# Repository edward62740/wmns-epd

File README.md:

# WMNS-EPD
Simple Wi-Fi/BLE enabled e-paper display. Designed for displaying real-time sensor data. Extention of [WMNS](https://github.com/edward62740/Wireless-Mesh-Network-System).</br></br>

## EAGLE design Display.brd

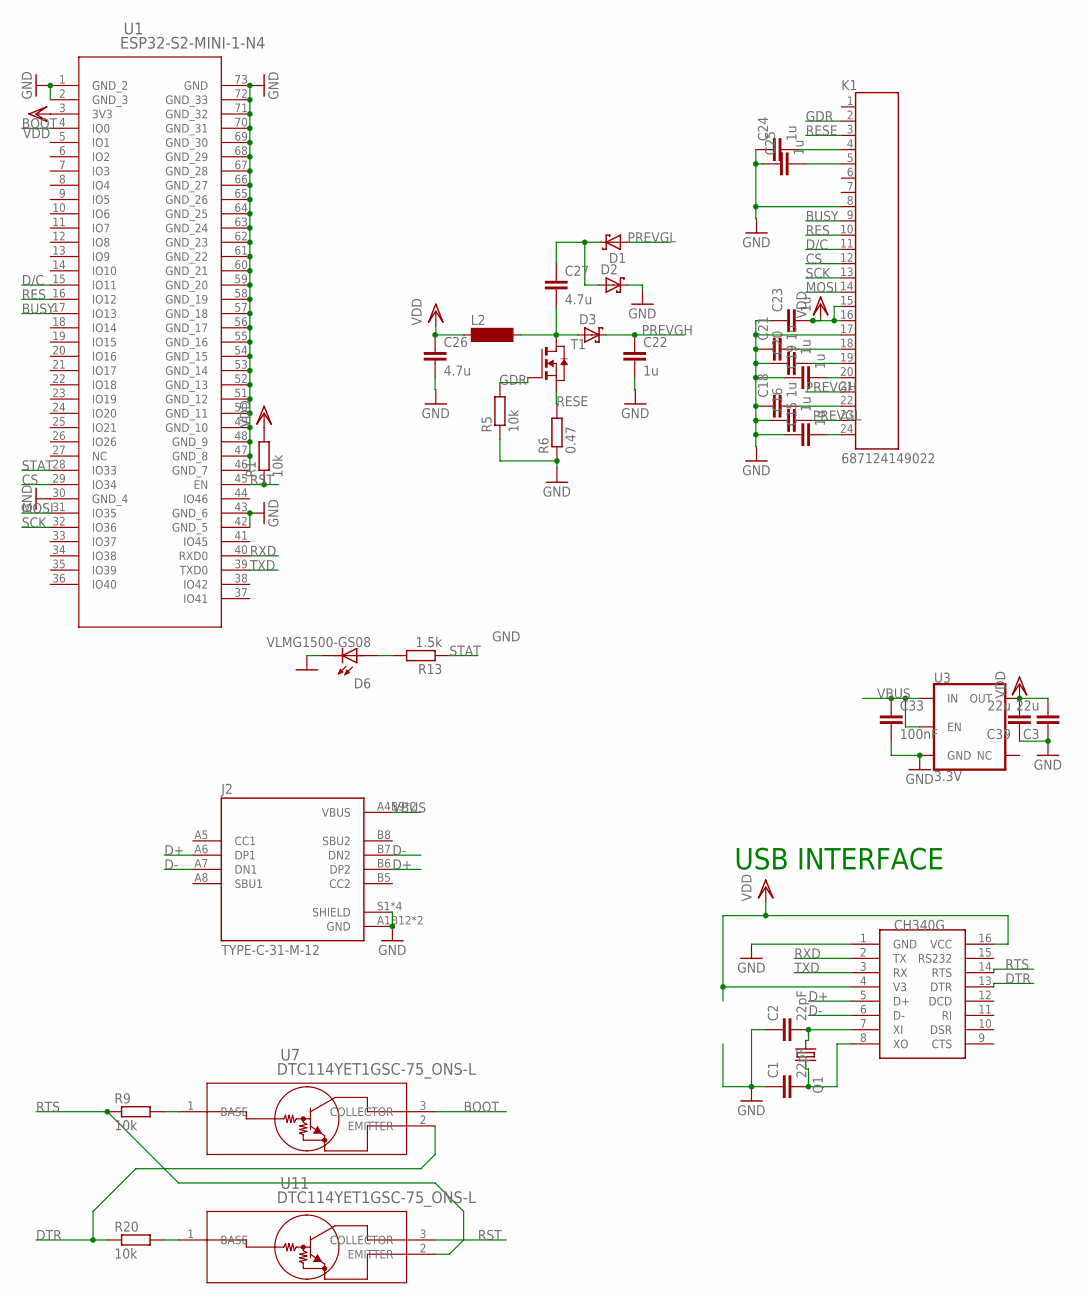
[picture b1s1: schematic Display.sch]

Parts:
C1, C2: 22pF; C0402
C3, C39: 22u; C0603R
C15, C16, C18, C19, C20, C21, C22, C23, C24, C25: 1u; C0402
C26, C27: 4.7u; C0402
C33: 100nF; C0402
D1, D2, D3: 1PS79SB30,115; SOD523
D6: VLMG1500-GS08; LEDC1005X35N
J2: TYPE-C-31-M-12; HRO_TYPE-C-31-M-12
K1: 687124149022
L2: SM-NE29
Q1: KX-7; 3.2X2.5_KX-7
R1, R5, R9, R20: 10k; R0402
R6: 0.47; R0402
R13: 1.5k; R0402
T1: NMOSSOT23; SOT-23
U1: ESP32-S2-MINI-1-N4; ESP32-S2-MINI-1-N4_EXP
U3: 3.3V; SOT23-5
U5: H; SOIC16
U7, U11: DTC114YET1GSC-75_ONS-L; SC-75_ONS-L

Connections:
BOOT: U1.4 (IO0), U7.3 (COLLECTOR)
BUSY: K1.9, U1.17 (IO13)
CS: K1.12, U1.29 (IO34)
D+: J2.A6 (DP1), J2.B6 (DP2), U5.5 (D+)
D-: J2.A7 (DN1), J2.B7 (DN2), U5.6 (D-)
D/C: K1.11, U1.15 (IO11)
DTR: R20.1, U5.13 (DTR), U7.2 (EMITTER)
GDR: K1.2, R5.2, T1.3 (G)
GND: C1.1, C2.1, C3.1, C15.1, C16.1, C18.1, C19.1, C20.1, C21.1, C22.2, C23.1, C24.1, C25.1, C26.2, C33.2, C39.1, D2.1 (K), D6.2, J2.A1B12 (GND), J2.B1A12 (GND), J2.S1 (SHIELD), J2.S2 (SHIELD), J2.S3 (SHIELD), J2.S4 (SHIELD), K1.8, K1.17, R5.1, R6.1, U1.1 (GND_2), U1.2 (GND_3), U1.30 (GND_4), U1.42 (GND_5), U1.43 (GND_6), U1.46 (GND_7), U1.47 (GND_8), U1.48 (GND_9), U1.49 (GND_10), U1.50 (GND_11), U1.51 (GND_12), U1.52 (GND_13), U1.53 (GND_14), U1.54 (GND_15), U1.55 (GND_16), U1.56 (GND_17), U1.57 (GND_18), U1.58 (GND_19), U1.59 (GND_20), U1.60 (GND_21), U1.61 (GND_22), U1.62 (GND_23), U1.63 (GND_24), U1.64 (GND_25), U1.65 (GND_26), U1.66 (GND_27), U1.67 (GND_28), U1.68 (GND_29), U1.69 (GND_30), U1.70 (GND_31), U1.71 (GND_32), U1.72 (GND_33), U1.73 (GND), U3.2 (GND), U5.1 (GND)
MOSI: K1.14, U1.31 (IO35)
unnamed: C1.2, Q1.3 (2), U5.8 (XO)
unnamed: C27.2, D3.2 (A), L2.2, T1.1 (D)
unnamed: C21.2, K1.18
unnamed: C2.2, Q1.1, U5.7 (XI)
unnamed: C18.2, K1.22
unnamed: C20.2, K1.19
unnamed: C19.2, K1.20
unnamed: C15.2, K1.24
unnamed: C24.2, K1.4
unnamed: C25.2, K1.5
unnamed: C27.1, D1.1 (K), D2.2 (A)
unnamed: D6.1, R13.2
unnamed: R20.2, U11.1 (BASE)
unnamed: R9.2, U7.1 (BASE)
PREVGH: C22.1, D3.1 (K), K1.21
PREVGL: C16.2, D1.2 (A), K1.23
RES: K1.10, U1.16 (IO12)
RESE: K1.3, R6.2, T1.2 (S)
RST: R1.1, U1.45 (EN), U11.3 (COLLECTOR)
RTS: R9.1, U5.14 (RTS), U11.2 (EMITTER)
RXD: U1.40 (RXD0), U5.2 (TX)
SCK: K1.13, U1.32 (IO36)
STAT: R13.1, U1.28 (IO33)
TXD: U1.39 (TXD0), U5.3 (RX)
VBUS: C33.1, J2.A4B9 (VBUS), J2.B4A9 (VBUS), U3.1 (IN), U3.3 (EN)
VDD: C3.2, C23.2, C26.1, C39.2, K1.15, K1.16, L2.1, R1.2, U1.3 (3V3), U3.5 (OUT), U5.4 (V3), U5.16 (VCC)

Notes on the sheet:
USB INTERFACE

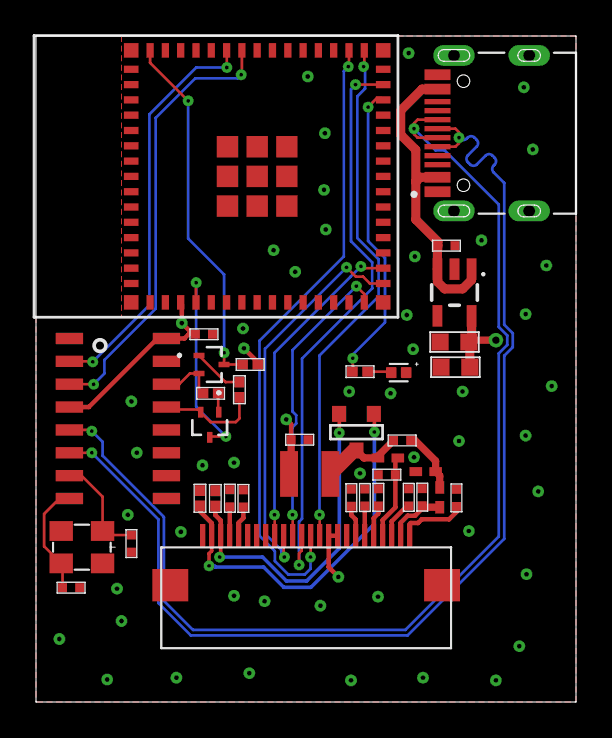
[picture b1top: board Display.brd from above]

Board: 4 copper layers, 30.0 x 37.0 mm, 37 parts (0 on the bottom side), 36 nets.

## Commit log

2022-03-15 Added PCB
2022-05-28 Added auto reconnect wifi
2022-06-12 Added display power down to prevent screen fading
2022-06-24 Fixed power off issue in GxEPD2_154_Z90c.cpp
    This issue caused fading display over time.
    Changed value of register 0x22 from 0xc3 (invalid) -> 0x03 per datasheet (https://v4.cecdn.yun300.cn/100001_1909185148/GDEH0154Z90-0111.pdf)

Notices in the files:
parts and their libraries:
SparkFun-IC-Power: Licensing: Creative Commons ShareAlike 4.0 International - https://creativecommons.org/licenses/by-sa/4.0
crystal-geyer_V1_0: Copyright: Geyer-Electronic
COPYRIGHT: Copyright (C) 2022 Ultra Librarian. All rights reserved.
